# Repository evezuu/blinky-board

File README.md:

# blinky-board
<br> I made a star-shaped board with blinking lights using KiCad. I did this by following the Hack Club tutorial. It has 10 different LEDs that flash whenever it's turned on.
From this, I learned the basics of KiCad and how it works. <br/>

<br> PCB: <br/>

<br> Schematic: <br/>

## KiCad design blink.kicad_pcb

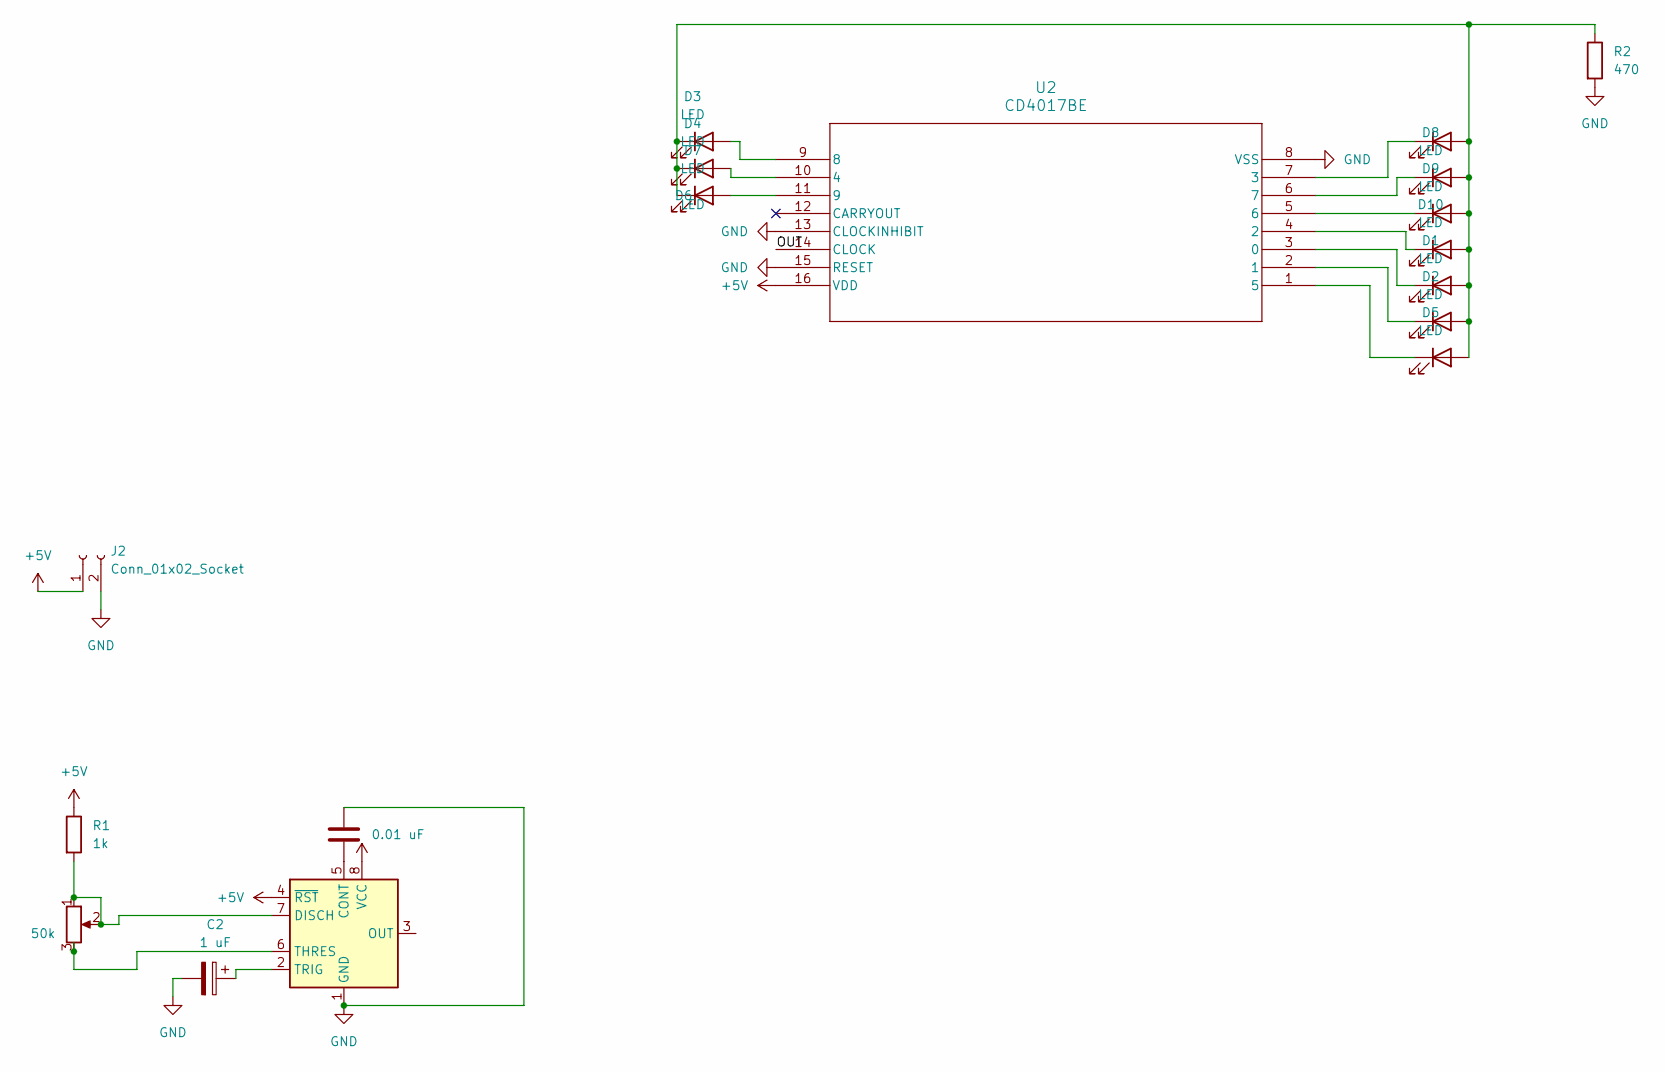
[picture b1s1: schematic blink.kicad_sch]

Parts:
C2: 1 uF; CP_Radial_D5.0mm_P2.00mm
C3: 0.01 uF; C_Disc_D7.5mm_W2.5mm_P5.00mm
D1, D2, D3, D4, D5, D6, D7, D8, D9, D10: LED; LED_D3.0mm
J2: Conn_01x02_Socket; PinHeader_1x02_P2.54mm_Vertical
R1: 1k; R_Axial_DIN0207_L6.3mm_D2.5mm_P7.62mm_Horizontal
R2: 470; R_Axial_DIN0207_L6.3mm_D2.5mm_P7.62mm_Horizontal
RV1: 50k; Potentiometer_Vishay_T93YA_Vertical
U1: NE555P; DIP-8_W7.62mm
U2: CD4017BE; N16

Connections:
+5V: J2.1, R1.1, U1.4 (~RST), U1.8 (VCC), U2.16 (VDD)
/OUT: U2.14 (CLOCK)
GND: C2.2, C3.1, J2.2, R2.2, U1.1 (GND), U2.8 (VSS), U2.13 (CLOCKINHIBIT), U2.15 (RESET)
unnamed: D1.2 (A), D2.2 (A), D3.1 (K), D4.1 (K), D5.2 (A), D6.2 (A), D7.1 (K), D8.2 (A), D9.2 (A), D10.2 (A), R2.1
unnamed: D1.1 (K), U2.3 (0)
unnamed: D2.1 (K), U2.2 (1)
unnamed: D3.2 (A), U2.9 (8)
unnamed: D4.2 (A), U2.10 (4)
unnamed: D5.1 (K), U2.1 (5)
unnamed: D6.1 (K), U2.7 (3)
unnamed: D7.2 (A), U2.11 (9)
unnamed: D8.1 (K), U2.6 (7)
unnamed: D9.1 (K), U2.5 (6)
unnamed: D10.1 (K), U2.4 (2)
unnamed: C3.2, U1.5 (CONT)
unnamed: R1.2, RV1.1, RV1.2, U1.7 (DISCH)
unnamed: RV1.3, U1.6 (THRES)
unnamed: C2.1, U1.2 (TRIG)

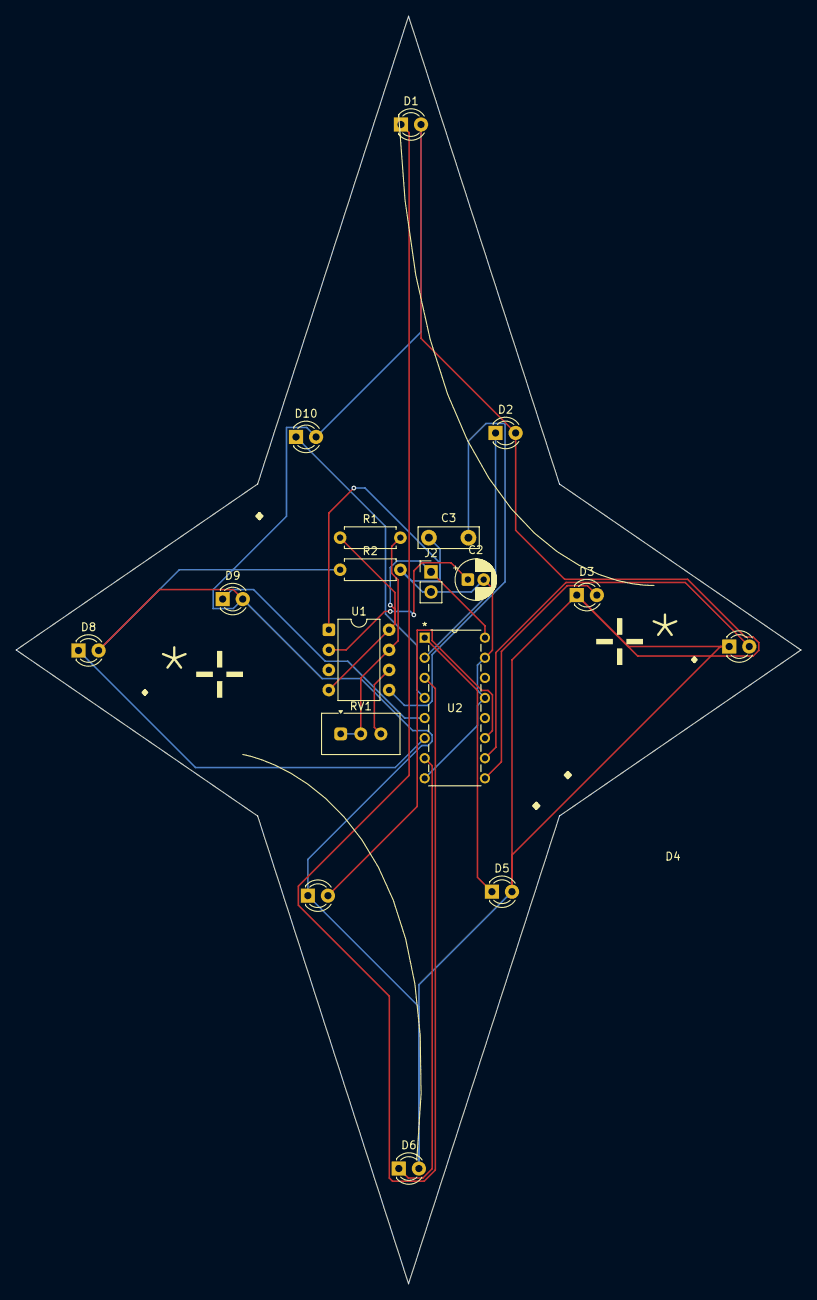
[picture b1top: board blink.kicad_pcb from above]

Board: 2 copper layers, 99.2 x 160.3 mm, 18 parts (0 on the bottom side), 17 nets.
